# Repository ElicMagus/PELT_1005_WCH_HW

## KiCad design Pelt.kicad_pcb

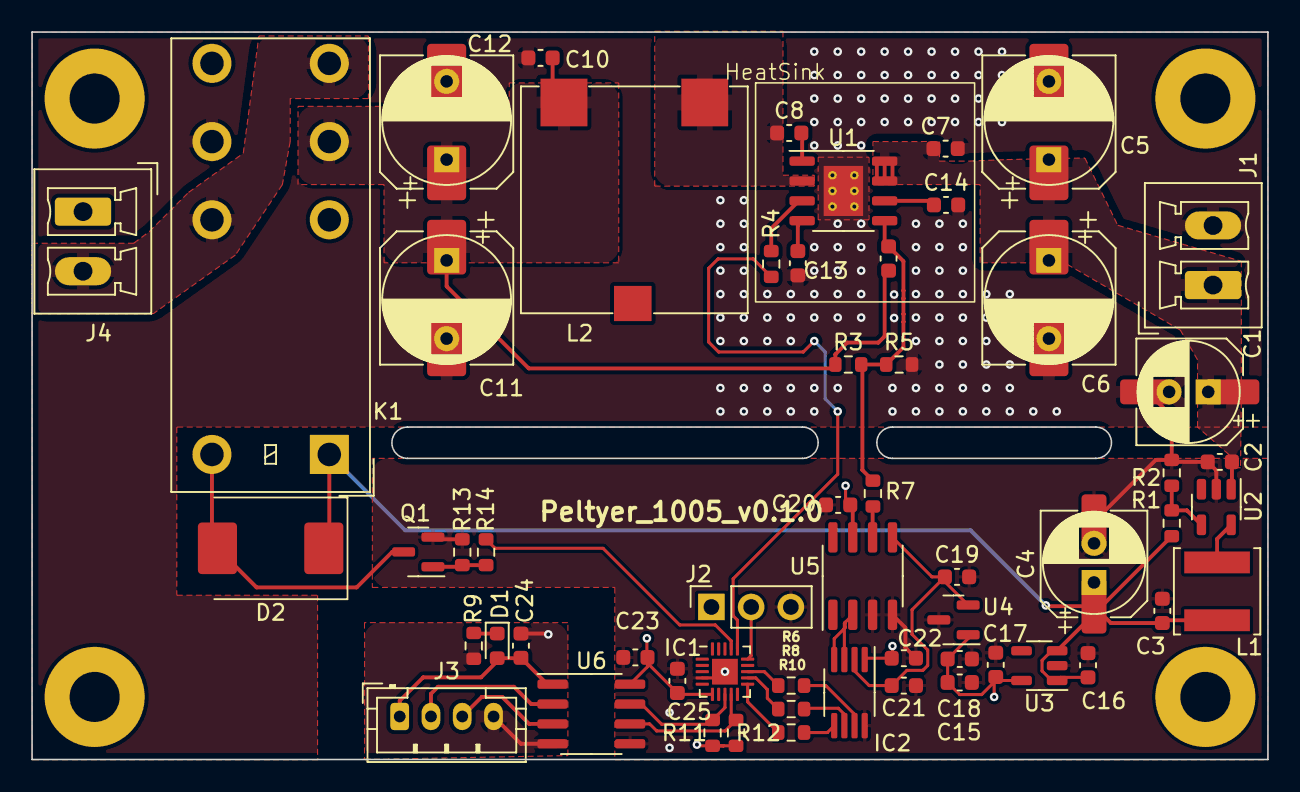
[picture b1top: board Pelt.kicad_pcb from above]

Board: 4 copper layers, 79.0 x 46.5 mm, 64 parts (0 on the bottom side), 36 nets.

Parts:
C1, C4: 100uF; CP_Elec_6.3x7.7
C1#2, C1#3: CP_Radial_D6.3mm_P2.50mm
C2, C3, C14, C16, C17, C21: 1uF; C_0603_1608Metric
C5, C6, C11#2, C12#2: 150uF; CP_Elec_8x10
C5#2, C6#2, C11, C12: CP_Radial_D8.0mm_P5.00mm
C7, C10, C15: 10uF; C_0603_1608Metric
C8, C13, C18, C19, C20, C22, C23, C24, C25: 0.1uF; C_0603_1608Metric
C9: 100pF; C_0603_1608Metric
D1: BLUE; LED_0603_1608Metric
D2: B320; D_SMC
HeatSink: HeatSink_14x14mm
IC1: CH32V003F4U6; QFN-20-1EP_3x3mm_P0.4mm_EP1.65x1.65mm
IC2: TPC116S1-VR; MSOP-8_3x3mm_P0.65mm
J1: Питание; PhoenixContact_MCV_1,5_2-G-3.81_1x02_P3.81mm_Vertical
J2: SWIO; PinSocket_1x03_P2.54mm_Vertical
J3: I2C_Connect; JST_PH_B4B-PH-K_1x04_P2.00mm_Vertical
J4: Модуль; PhoenixContact_MCV_1,5_2-G-3.81_1x02_P3.81mm_Vertical
K1: IM00; Relay_DPDT_Omron_G2RL
L1: 47uH; L_Changjiang_FNR5012S
L2: 6.1uH; CDEP147NP-6R1MC-125
Q1: AO3400A; SOT-23
R1: 36k; R_0603_1608Metric
R2, R4, R5, R11, R12, R14: 10k; R_0603_1608Metric
R3: 120k; R_0603_1608Metric
R6, R8, R9, R10, R13: 200; R_0603_1608Metric
R7: 30k; R_0603_1608Metric
U1: SY8205FCC; SOIC-8-1EP_3.9x4.9mm_P1.27mm_EP2.514x3.2mm_ThermalVias
U2: AP2900; SOT-23-5
U3: TPL903250; SOT-23-5
U4: RS3112-2.5; SOT-23
U5: TPA1286U-VS1R; SOIC-8_3.9x4.9mm_P1.27mm
U6: NSI8100N; SOIC-8_3.9x4.9mm_P1.27mm

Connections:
+5.5V: C1#2.1, C3.1, C4.1, C16.1, D2.1 (K), K1.1, L1.2, R1.1, U3.1 (IN), U3.3 (EN)
+5V: C15.1, C17.1, C18.1, C20.1, C22.1, C23.2, C25.2, IC1.6 (VDD), IC2.1 (VDD), J2.1, R11.2, R12.2, U3.5 (OUT), U4.1 (IN), U5.7 (V+), U6.8 (VCC2)
/LX: C8.1, L2.1, U1.2 (LX)
/Minus: J4.2, K1.4, K1.7
/Plus: J4.1, K1.2, K1.5
/U_Set: IC2.3 (VFB), IC2.4 (VOUT), U5.2 (-)
/V_out: C9.1, C10.1, C11.1, C11#2.1, C12.1, C12#2.1, K1.3, L2.2, R3.1
EN_A: IC1.17 (PD3), R13.2
GND: C1.2, C1#2.2, C1#3.2, C2.2, C3.2, C4.2, C5.2, C5#2.2, C6.2, C6#2.2, C7.2, C10.2, C11.2, C11#2.2, C12.2, C12#2.2, C13.2, C14.2, C15.2, C16.2, C17.2, C18.2, C19.2, C20.2, C21.1, C22.2, C23.1, C25.1, IC1.4 (VSS), IC1.21 (VSS), IC2.8 (GND), J1.2, J2.3, K1.6, Q1.2 (S), R2.2, R5.2, R14.1, U1.9 (GND), U2.2 (GND), U3.2 (GND), U4.3 (GND), U5.3 (+), U5.4 (V-), U6.5 (GND2)
unnamed: C24.2, D1.2 (A), J3.1, U6.1 (VCC1)
unnamed: D1.1 (K), R9.1
unnamed: D2.2 (A), K1.8, Q1.3 (D)
unnamed: IC1.11 (PC4), R10.1
unnamed: IC1.12 (SCK), R8.1
unnamed: IC1.13 (MOSI), R6.1
unnamed: IC1.15 (SWIO), J2.2
unnamed: IC2.7 (DIN), R6.2
unnamed: IC2.6 (SCLK), R8.2
unnamed: IC2.5 (~SYNC), R10.2
unnamed: J3.2, U6.2 (SDA1)
unnamed: J3.3, U6.3 (SCL1)
unnamed: C24.1, J3.4, R9.2, U6.4 (GND1)
unnamed: Q1.1 (G), R13.1, R14.2
unnamed: R7.1, U5.6
unnamed: C8.2, U1.1 (BS)
unnamed: R4.2, U1.3 (EN)
unnamed: C13.1, U1.4 (SS)
unnamed: C14.1, U1.6 (Vcc)
unnamed: R1.2, R2.1, U2.4 (FB)
unnamed: L1.1, U2.5 (SW)
SCL: IC1.9 (SCL), R12.1, U6.6 (SCL2)
SDA: IC1.8 (SDA), R11.1, U6.7 (SDA2)
SHDWN: IC1.16 (PD2), R4.1
U_ref: C19.1, C21.2, IC2.2 (VREF), U4.2 (OUT), U5.5 (Ref)
Vfb: C9.2, R3.2, R5.1, R7.2, U1.5 (FB)
Vin: C1.1, C1#3.1, C2.1, C5.1, C5#2.1, C6.1, C6#2.1, C7.1, J1.1, U1.7 (Vin), U1.8 (Vin), U2.1 (VI)

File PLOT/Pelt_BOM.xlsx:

Reference | Value | Footprint | PartNumber | Цена | Кол. | Сумма
C8, C13, C18-C20, C22-C25 | 0.1uF | Capacitor_SMD:C_0603_1608Metric | GRM188R71H104KA93D | 0.28000000000000003 | 9 | 2.5200000000000005
C9 | 100pF | Capacitor_SMD:C_0603_1608Metric | GRM1885C1H101JA01D | 0.37 | 1 | 0.37
C2, C7, C10 | 1uF | Capacitor_SMD:C_0603_1608Metric | TCC0603X7R105K350CT | 0.91 | 3 | 2.73
C3, C14, C16, C17, C21 | 1uF | Capacitor_SMD:C_0603_1608Metric | TCC0603X7R105K250CT / CC0603JRX7R7BB105 | 0.21 | 5 | 1.05
L2 | 6.1uH | SamacSys_Parts:CDEP147NP-6R1MC-125 | CDEP147NP-6R1MC-125 | 94.84 | 1 | 94.84
C15 | 10uF | Capacitor_SMD:C_0603_1608Metric |  | 0.38 | 1 | 0.38
L1 | 47uH | Inductor_SMD:L_Changjiang_FNR5012S | CDRH4D28NP-470NC | 28.76 | 1 | 28.76
C1, C4 | 100uF | Capacitor_SMD:CP_Elec_6.3x7.7 | EEEFPV101XAP | 24.06 | 2 | 48.12
C5, C6, C11, C12 | 150uF | Capacitor_SMD:CP_Elec_8x10 | EEHZA1V151P | 53.94 | 4 | 215.76
R6, R8-R10, R13 | 240 | Resistor_SMD:R_0603_1608Metric | RC0603FR-07240RL | 0.13 | 5 | 0.65
R2, R4, R5, R11, R12, R14 | 10k | Resistor_SMD:R_0603_1608Metric | RC0603FR-0710KL | 0.08 | 6 | 0.48
R7 | 30k | Resistor_SMD:R_0603_1608Metric | RC0603FR-0730KL | 0.08 | 1 | 0.08
R1 | 36k | Resistor_SMD:R_0603_1608Metric | RC0603FR-0736KL | 0.14000000000000001 | 1 | 0.14000000000000001
R3 | 120k | Resistor_SMD:R_0603_1608Metric | RC0603FR-07120KL | 0.09 | 1 | 0.09
Q1 | AO3400A | Package_TO_SOT_SMD:SOT-23 | AO3400A | 2.21 | 1 | 2.21
U2 | AP2900 | Package_TO_SOT_SMD:SOT-23-5 | AP2900TB-A1 | 16.02 | 1 | 16.02
D2 | B320 | Diode_SMD:D_SMC | 30BQ060-SMC (KLS) | 11.3 | 1 | 11.3
D1 | BLUE | LED_SMD:LED_0603_1608Metric | FYLS-0603BUBC | 2.8 | 1 | 2.8
IC1 | CH32V003F4U6 | Package_DFN_QFN:QFN-20-1EP_3x3mm_P0.4mm_EP1.65x1.65mm | CH32V003F4U6 | 16.100000000000001 | 1 | 16.100000000000001
J3 | I2C_Connect | Connector_JST:JST_PH_B4B-PH-K_1x04_P2.00mm_Vertical | L-KLS1-XL1-2.00-04-S | 0.76 | 1 | 0.76
K1 | IM00 | Relay_THT:Relay_DPDT_Omron_G2RL | HF115F/005-2Z4B | 124.48 | 1 | 124.48
U6 | NSI8100NC | Package_SO:SOIC-8_3.9x4.9mm_P1.27mm | NSI8100NC | 85.13 | 1 | 85.13
U4 | RS3112-2.5 | Package_TO_SOT_SMD:SOT-23 | RS3112-2.5XSF3 | 66.87 | 1 | 66.87
U3 | RS3236-5.0AYF5 | Package_TO_SOT_SMD:SOT-23-5 | RS3236-5.0AYF5 | 3.12 | 1 | 3.12
U1 | SY8205FCC | Package_SO:SOIC-8-1EP_3.9x4.9mm_P1.27mm_EP2.514x3.2mm_ThermalVias | SY8205FCC | 41.58 | 1 | 41.58
U5 | TPA1286 | Package_SO:SOIC-8_3.9x4.9mm_P1.27mm | TPA1286-SO1R | 81.96 | 1 | 81.96
IC2 | TPC116S1-VR | Package_SO:MSOP-8_3x3mm_P0.65mm | TPC116S1-VR | 149.13999999999999 | 1 | 149.13999999999999
J4 | Модуль | Connector_Phoenix_MC:PhoenixContact_MCV_1,5_2-G-3.81_1x02_P3.81mm_Vertical | 15EDGVC-3.81-02P-14-00AH | 6.11 | 1 | 6.11
J1 | Питание | Connector_Phoenix_MC:PhoenixContact_MCV_1,5_2-G-3.81_1x02_P3.81mm_Vertical | 15EDGVC-3.81-02P-14-00AH | 6.11 | 1 | 6.11
 |  |  |  |  | Итого | 1009.66

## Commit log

2024-04-08 v0.1.0
